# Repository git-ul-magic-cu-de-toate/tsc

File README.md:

<!-- readme-generat -->
<div align="center">

# 📚 TSC

*Arhivă de materiale din ani anteriori · Facultatea de Automatică și Calculatoare (ACS), UNSTPB*

</div>

---

## 👋 Despre acest repo

Acest repository adună **materialele pentru TSC** strânse de-a lungul mai multor ani și de la mai mulți colegi: cursuri, laboratoare, teme, subiecte de examen și parțial, rezolvări și resurse suplimentare.

Scopul lui este să fie un punct de pornire pentru cei care parcurg materia în anii următori. Materialele provin din Anul 3, Sem. 2 · Anul 4, Sem. 2.

> 💡 **Sfat:** începe cu directoarele `curs` / `cursuri` pentru teorie, apoi `laboratoare` pentru practică, iar spre final uită-te la `examen` și `partial` ca să vezi ce se cere de obicei.

## 🗂️ Ce găsești aici

| Director | Ce conține | Fișiere | Dimensiune |
|---|---|---:|---:|
| 📁 `colocviu/` | Colocviu: subiecte și rezolvări | 26 | 20.0 MB |
| 📁 `curs/` | Cursuri: slide-uri, PDF-uri și notițe | 17 | 43.8 MB |
| 📁 `diverse/` | Diverse: resurse care nu se încadrează în celelalte categorii | 2 | 53.0 MB |
| 📁 `labs/` | Laboratoare: enunțuri, resurse și rezolvări | 126 | 31.2 MB |
| 📁 `old/` | Materiale din ani anteriori | 66 | 54.6 MB |
| 📁 `proiect/` | Teme și proiecte | 29 | 14.1 MB |
| 📁 `subiecte/` | Subiecte (examen/parțial/colocviu) | 7 | 2.1 MB |
| 📁 `tsc/` |  | 0 | 0 B |

## 🌳 Structura repo-ului

```text
tsc/
├── colocviu/                                   # Colocviu: subiecte și rezolvări
│   └── … încă 26 fișiere
├── curs/                                       # Cursuri: slide-uri, PDF-uri și notițe
│   ├── Anul 3 - Sem 2/                         # 1 fișiere (pdf×1)
│   │   └── pdf/                                # Materiale în format PDF
│   ├── teste_2024/                             # 4 fișiere (pdf×4)
│   │   └── … încă 4 fișiere
│   └── … încă 12 fișiere
├── diverse/                                    # Diverse: resurse care nu se încadrează în celelalte categorii
│   └── Anul 3 - Sem 2/                         # 2 fișiere (pdf×2)
│       └── … încă 2 fișiere
├── labs/                                       # Laboratoare: enunțuri, resurse și rezolvări
│   ├── Anul 3 - Sem 2/                         # 72 fișiere (py×24, png×20, js×6)
│   │   ├── lab05/                              # Laboratorul 5
│   │   ├── lab06/                              # Laboratorul 6
│   │   ├── lab07/                              # Laboratorul 7
│   │   └── lab08/                              # Laboratorul 8
│   ├── lab07/                                  # Laboratorul 7
│   │   └── tree-traversal/                   
│   ├── pdf lab tsc/                            # 10 fișiere (pdf×10)
│   │   └── … încă 10 fișiere
│   ├── SparkFun-Eagle-Libraries-main/          # 39 fișiere (lbr×33, png×3, zip×1)
│   │   ├── SparkFun-Eagle-Libraries-main/      # 38 fișiere (lbr×33, png×3, md×1)
│   │   └── … încă 1 fișiere
│   └── … încă 3 fișiere
├── old/                                        # Materiale din ani anteriori
│   ├── Cheatsheets/                            # 1 fișiere (pdf×1)
│   │   └── … încă 1 fișiere
│   ├── Grile/                                  # 1 fișiere (pdf×1)
│   │   └── … încă 1 fișiere
│   ├── lab1/                                   # Laboratorul 1
│   │   ├── adafruit-Adafruit-Eagle-Library-4abf84c/  # 3 fișiere (md×1, lbr×1, txt×1)
│   │   └── … încă 24 fișiere
│   ├── Proiect/                                # Teme și proiecte
│   │   └── … încă 26 fișiere
│   ├── Subiecte Examen/                        # Subiecte (examen/parțial/colocviu)
│   │   └── … încă 5 fișiere
│   └── Teorie/                                 # 4 fișiere (pdf×4)
│       ├── Curs & Lab/                         # 2 fișiere (pdf×2)
│       └── Extra/                              # 2 fișiere (pdf×2)
├── proiect/                                    # Teme și proiecte
│   ├── Anul 3 - Sem 2/                         # 2 fișiere (pdf×1, txt×1)
│   │   ├── Minea_RaduStefan_334CA_before_deadline/  # 1 fișiere (txt×1)
│   │   └── … încă 1 fișiere
│   ├── hector_watch/                           # 1 fișiere (lbr×1)
│   │   └── … încă 1 fișiere
│   └── … încă 26 fișiere
├── subiecte/                                   # Subiecte (examen/parțial/colocviu)
│   ├── Anul 3 - Sem 2/                         # 6 fișiere (pdf×3, jpeg×2, jpg×1)
│   │   └── serie_necunoscuta/                  # Materiale a căror serie nu a putut fi identificată
│   └── … încă 1 fișiere
└── tsc/                                      
```

## 🧭 Cum te orientezi

- Seriile **CA, CB, CC, CD** (anii 1–3) și direcțiile **C1–C5** (anul 4) au profesori și cerințe diferite; unde seria era cunoscută, materialele sunt grupate pe serie.
- Directoarele `serie_necunoscuta` conțin materiale a căror serie nu a putut fi stabilită.
- Directoarele `labNN` / `Laborator NN` corespund laboratoarelor în ordine cronologică.
- Fișierele cu același nume dar conținut diferit au fost păstrate (de exemplu în `duplicate/` sau cu sufixul `__local`), ca să nu se piardă nimic.

## 📊 Pe scurt

- **277** fișiere, **218.9 MB** în total
- Tipuri frecvente: `.pdf` ×48 · `.lbr` ×36 · `.jpg` ×28 · `.png` ×25 · `.py` ×24 · `.job` ×14

## ⚠️ De reținut

- Materialele provin din ani și de la profesori diferiți; cerințele, baremele și tehnologiile pot fi diferite față de anul curent.
- Rezolvările și temele colegilor sunt doar pentru **studiu și inspirație**. Folosește-le cu responsabilitate și respectă regulile de integritate academică ale materiei.
- Pot exista greșeli sau materiale depășite. Verifică mereu cu cerințele oficiale ale cursului.

## 🤝 Contribuții

Ai materiale noi, corecturi sau vrei să ajuți la completarea arhivei? Scrie-mi pe email:

📧 **[sciencepc@yahoo.com](mailto:sciencepc@yahoo.com)**

Mulțumim tuturor celor care au contribuit! 💙

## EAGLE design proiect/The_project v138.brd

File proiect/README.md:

# Pasi de implementare

## 1. Acomodarea cu tematica 
- intelegere enunt si descarcare biblioteci necesare

## 2. Schematic
- am incercat sa fie cat mai asemanator cu imaginea pdf pusa pe ocw

## 3. PCB
- la generarea pcb-ului pe baza schematicului, piesele erau deja puse. 
- singurul lucru care a fost de modificat aici a fost forma butoanelor si a adaptorului. 
- am inceput cu butoanele caci au fost mai simplu. am incercat sa ma tin cat mai aproape de dimensiunile din datasheet-uri. ca sa am dimensiunile convenabile am setat gridul la 0.1 mm pentru o precizie sporita.
- acelasi lucru si la adaptorul lcd, unde am facut cateva calcule spre aflarea tuturor dimensiunilor necesare. aici a trebuit sa modific schematicul adaptorului, pinii MP1 si MP2 nefiind necesari.

## 4. Pregatire pentru "asamblare"
- am grupat componentele dupa cum erau grupate in schematic, pentru o asezare mai usoara pe planul ceasului.
- am folosit mirror pentru a pune componentele de pe bottom conform cerintei, asta inca din acest punct, pentru a vizualiza mai usor planurile

## 5. Forma ceas
- apoi am creat forma ceasului, la fel, cu multe ajustari, dupa dimensiuni (am incercat sa fac sa intre in carcasa).

## 6. GND
- am creat planul de masa cu polygon pour si linie care se poate curba, incercand cu greu sa tin conturul ceasului. copy-paste pentru bottom, selectat impruna si redenumit (legat) la GND.

## 7. Punere elemente
- am pus toate elementele in interiorul formei de ceas, incercand pe cat posibil sa pastrez restrictiile (condensatoarele fiecarui tip de piesa cat mai aproape de pini) (evebtual asa si la rezistente). 
- am pus antena pe mijloc, la margini sd-reader-ul si usb-ul, pe langa si celelalte piese, la fel, am incercat sa nu pun nor-flash sub antena pe planul de desesubt.

## 8. Finisare PCB
- am taiat forma de ceas, stergand pcb-ul, ramanand numai cercul ceasului cu planurile de masa si piesele.

## 9. Rutare
- am trecut de data aceasta la auto-route, dupa lungi incercari de a ruta manual si a reaseza piesele pentru o rutare manuala mai usoara.
- si la auto-route a trebuit sa rearanjez piesele de cateva ori (respectand restrictiile) pentru o eficienta mai sportita (88-100% routing).
chiar si asa am avut 5 air-wires.

## 10. Ajustare dupa auto-route
- am inlocuit grosimea firelor de putere (GND, VIBE-OUT, VBUS, VUSB, 3V3 etc). in acest proces mi-au aparut multe overlap-uri.
- acest lucru l-am facut ori schimbat grosmiea firului din proprieteti, ori stergandu-l si trasandu-l la loc, acolo unde am avut loc.
- pe anumite portiuni am combinatie de 0.127 - 0.3 mm

## 11. Altele
- am un overlap la un footprint care nu a fost realizat sau modificat de mine.

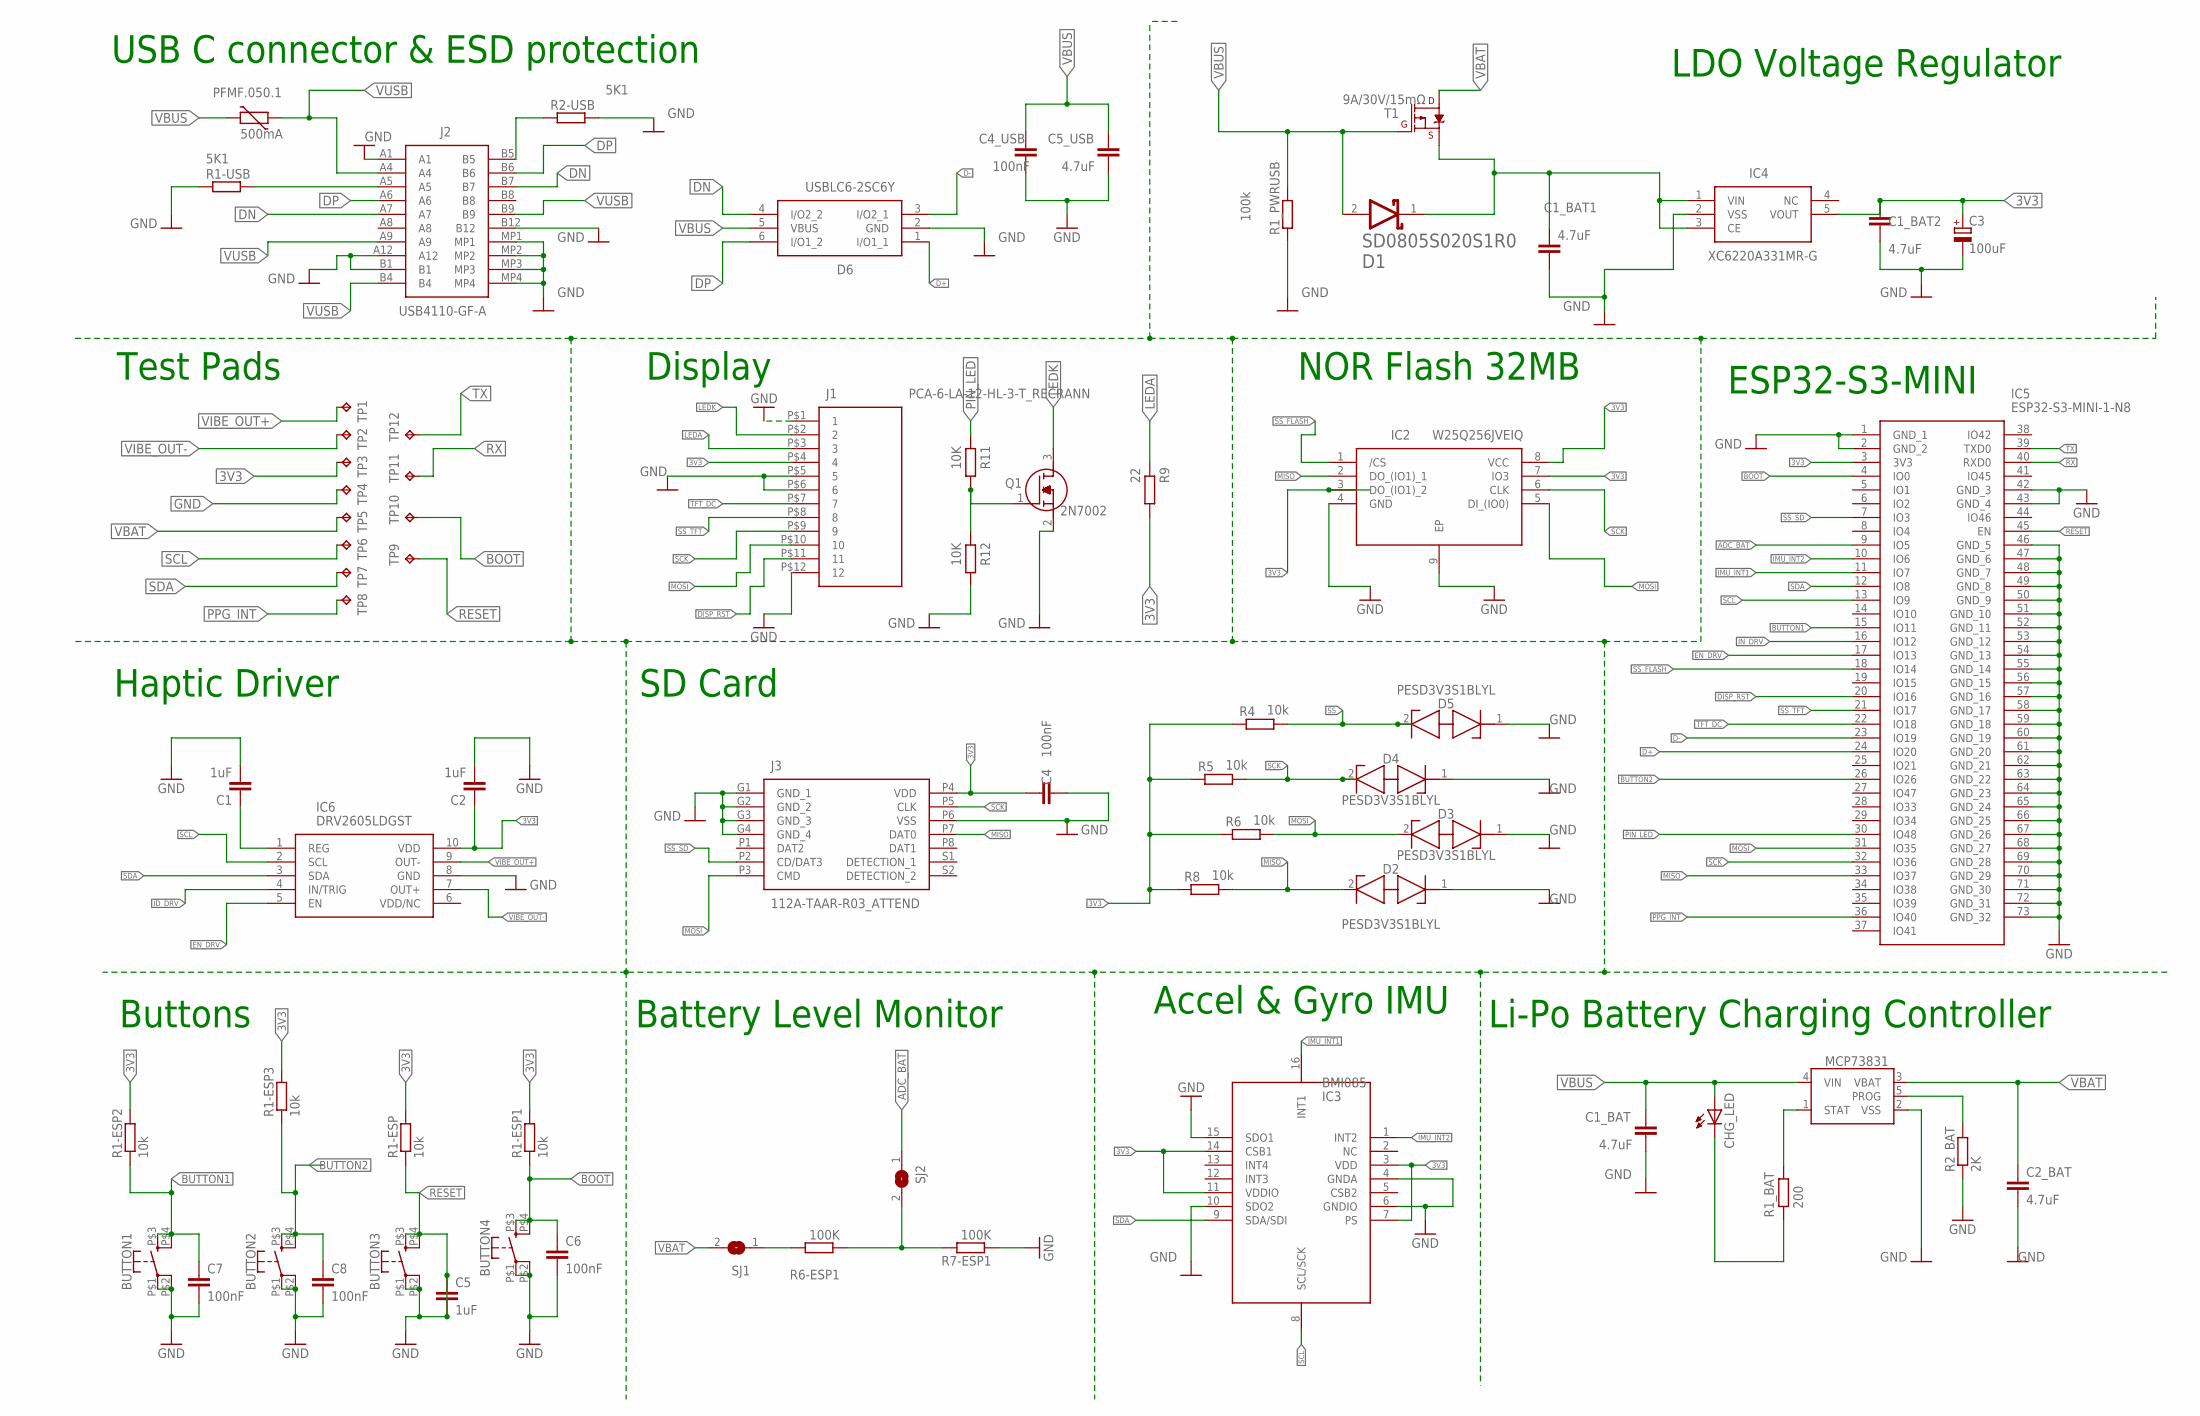
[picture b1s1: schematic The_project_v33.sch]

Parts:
BUTTON1, BUTTON2, BUTTON3, BUTTON4: SPARKFUN-SWITCHES_MOMENTARY-SWITCH-SPST-2; RRR
C1, C2, C5: 1uF; EAGLE-LTSPICE_C0402
C1_BAT, C2_BAT: 4.7uF; EAGLE-LTSPICE_C0402
C1_BAT1, C1_BAT2, C5_USB: 4.7uF; RCL_C0603
C3: 100uF; CT3528
C4, C6, C7, C8: 100nF; EAGLE-LTSPICE_C0402
C4_USB: 100nF; RCL_C0603
CHG_LED: ADAFRUIT_LEDCHIP-LED0603; ADAFRUIT_CHIP-LED0603
D1: AVX---SD0805S020S1R0_AVX_SD0805S020S1R0AVX_SD0805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; AVX---SD0805S020S1R0_AVX_SD0805S020S1R0_0
D2, D3, D4, D5: PESD3V3S1BLYL; PESD5V0S1BL315
D6: USBLC6-2SC6Y; SOT95P280X145-6N
IC2: W25Q256JVEIQ; SON127P800X600X80-9N
IC3: BMI085
IC4: XC6220A331MR-G; SOT95P280X120-5N
IC5: ESP32-S3-MINI-1-N8; ESP32S3MINI1N8
IC6: DRV2605LDGST; SOP50P490X110-10N
J1: PCA-6-LA-12-HL-3-T_RECRANN; LCD
J2: USB4110-GF-A; USB4110GFA
J3: 112A-TAAR-R03_ATTEND; 112ATAARR03ATTEND
MCP73831: SPARKFUN-IC-POWER_MCP73831; SPARKFUN-IC-POWER_SOT23-5
PFMF.050.1: 500mA; VARISTOR_CT/CN1812
Q1: 2N7002; SOT96P240X120-3N
R1-ESP, R1-ESP1, R1-ESP2, R1-ESP3, R4, R5, R6, R8: 10k; EAGLE-LTSPICE_R0402
R1-USB, R2-USB: 5K1; EAGLE-LTSPICE_R0402
R1_BAT: 200; EAGLE-LTSPICE_R0402
R1_PWRUSB: 100k; EAGLE-LTSPICE_R0402
R2_BAT: 2K; EAGLE-LTSPICE_R0402
R6-ESP1, R7-ESP1: 100K; EAGLE-LTSPICE_R0402
R9: 22; EAGLE-LTSPICE_R0402
R11, R12: 10K; EAGLE-LTSPICE_R0402
SJ1, SJ2: SJ
T1: 9A/30V/15mΩ; SPARKFUN-DISCRETESEMI_SOT23-3
TP1, TP2, TP3, TP4, TP5, TP6, TP7, TP8, TP9, TP10, TP11, TP12: TPTP20R; TP20R

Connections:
3V3: C1_BAT2.1, C2.1, C3.+, C4.1, IC2.3 (DO_(IO1)_2), IC2.7 (IO3), IC2.8 (VCC), IC3.3 (VDD), IC3.7 (PS), IC3.11 (VDDIO), IC3.14 (CSB1), IC4.5 (VOUT), IC5.3 (3V3), IC6.10 (VDD), J1.P$4 (4), J3.P4 (VDD), R1-ESP.2, R1-ESP1.2, R1-ESP2.2, R1-ESP3.2, R4.1, R5.1, R6.1, R8.1, R9.1, TP3.TP
ADC_BAT: IC5.9 (IO5), SJ2.1
BOOT: BUTTON4.P$3 (3), BUTTON4.P$4 (4), C6.1, IC5.4 (IO0), R1-ESP1.1, TP10.TP
BUTTON1: BUTTON1.P$3 (3), BUTTON1.P$4 (4), C7.1, IC5.15 (IO11), R1-ESP2.1
BUTTON2: BUTTON2.P$3 (3), BUTTON2.P$4 (4), C8.1, IC5.26 (IO26), R1-ESP3.1
D+: IC5.24 (IO20)
D-: IC5.23 (IO19)
DISP_RST: IC5.20 (IO16), J1.P$11 (11)
DN: J2.A7, J2.B7
DP: J2.A6, J2.B6
EN_DRV: IC5.17 (IO13), IC6.5 (EN)
GND: BUTTON1.P$1 (1), BUTTON1.P$2 (2), BUTTON2.P$1 (1), BUTTON2.P$2 (2), BUTTON4.P$1 (1), BUTTON4.P$2 (2), C1.2, C1_BAT.2, C1_BAT1.2, C1_BAT2.2, C2.2, C2_BAT.2, C3.-, C4.2, C4_USB.2, C5_USB.2, C6.2, C7.2, C8.2, D2.1 (K1), D3.1 (K1), D4.1 (K1), D5.1 (K1), D6.2 (GND), IC2.4 (GND), IC2.9 (EP), IC3.4 (GNDA), IC3.6 (GNDIO), IC3.10 (SDO2), IC3.15 (SDO1), IC4.2 (VSS), IC5.1 (GND_1), IC5.2 (GND_2), IC5.42 (GND_3), IC5.43 (GND_4), IC5.46 (GND_5), IC5.47 (GND_6), IC5.48 (GND_7), IC5.49 (GND_8), IC5.50 (GND_9), IC5.51 (GND_10), IC5.52 (GND_11), IC5.53 (GND_12), IC5.54 (GND_13), IC5.55 (GND_14), IC5.56 (GND_15), IC5.57 (GND_16), IC5.58 (GND_17), IC5.59 (GND_18), IC5.60 (GND_19), IC5.61 (GND_20), IC5.62 (GND_21), IC5.63 (GND_22), IC5.64 (GND_23), IC5.65 (GND_24), IC5.66 (GND_25), IC5.67 (GND_26), IC5.68 (GND_27), IC5.69 (GND_28), IC5.70 (GND_29), IC5.71 (GND_30), IC5.72 (GND_31), IC5.73 (GND_32), IC6.8 (GND), J1.P$1 (1), J1.P$5 (5), J1.P$6 (6), J1.P$12 (12), J2.A1, J2.A12, J2.B1, J2.B12, J2.MP1, J2.MP2, J2.MP3, J2.MP4, J3.G1 (GND_1), J3.G2 (GND_2), J3.G3 (GND_3), J3.G4 (GND_4), J3.P6 (VSS), MCP73831.2 (VSS), Q1.2 (S), R1_PWRUSB.1, R2-USB.2, R2_BAT.1, R7-ESP1.1, R12.1, TP4.TP
ID_DRV: IC6.4 (IN/TRIG)
IMU_INT1: IC3.16 (INT1), IC5.11 (IO7)
IMU_INT2: IC3.1 (INT2), IC5.10 (IO6)
IN_DRV: IC5.16 (IO12)
LEDA: J1.P$3 (3), R9.2
LEDK: J1.P$2 (2), Q1.3 (D)
MISO: D2.2 (K2), IC2.2 (DO_(IO1)_1), IC5.33 (IO37), J3.P7 (DAT0), R8.2
MOSI: D3.2 (K2), IC2.5 (DI_(IO0)), IC5.31 (IO35), J1.P$10 (10), J3.P3 (CMD), R6.2
unnamed: J2.A5, R1-USB.2
unnamed: C1_BAT1.1, D1.1 (CATHODE), IC4.1 (VIN), IC4.3 (CE), T1.2 (S)
unnamed: R6-ESP1.2, SJ1.1
unnamed: Q1.1 (G), R11.1, R12.2
unnamed: R6-ESP1.1, R7-ESP1.2, SJ2.2
unnamed: J2.B5, R2-USB.1
unnamed: CHG_LED.C, R1_BAT.2
unnamed: C1.1, IC6.1 (REG)
unnamed: MCP73831.1 (STAT), R1_BAT.1
unnamed: MCP73831.5 (PROG), R2_BAT.2
PIN_LED: IC5.30 (IO48), R11.2
PPG_INT: IC5.36 (IO40), TP8.TP
RESET: BUTTON3.P$1 (1), BUTTON3.P$2 (2), BUTTON3.P$3 (3), BUTTON3.P$4 (4), C5.1, C5.2, IC5.45 (EN), R1-ESP.1, TP9.TP
RX: IC5.40 (RXD0), TP11.TP
SCK: D4.2 (K2), IC2.6 (CLK), IC5.32 (IO36), J1.P$9 (9), J3.P5 (CLK), R5.2
SCL: IC3.8 (SCL/SCK), IC5.13 (IO9), IC6.2 (SCL), TP6.TP
SDA: IC3.9 (SDA/SDI), IC5.12 (IO8), IC6.3 (SDA), TP7.TP
SS: D5.2 (K2), R4.2
SS_FLASH: IC2.1 (/CS), IC5.18 (IO14)
SS_SD: IC5.7 (IO3), J3.P2 (CD/DAT3)
SS_TFT: IC5.21 (IO17), J1.P$8 (8)
TFT_DC: IC5.22 (IO18), J1.P$7 (7)
TX: IC5.39 (TXD0), TP12.TP
VBAT: C2_BAT.1, MCP73831.3 (VBAT), SJ1.2, T1.3 (D), TP5.TP
VBUS: C1_BAT.1, C4_USB.1, C5_USB.1, CHG_LED.A, D1.2 (ANODE), MCP73831.4 (VIN), PFMF.050.1.2, R1_PWRUSB.2, T1.1 (G)
VIBE_OUT+: IC6.9 (OUT-), TP1.TP
VIBE_OUT-: IC6.7 (OUT+), TP2.TP
VUSB: J2.A4, J2.A9, J2.B4, PFMF.050.1.1

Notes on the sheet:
USB C connector & ESD protection
LDO Voltage Regulator
Test Pads
Display
NOR Flash 32MB
ESP32-S3-MINI
Haptic Driver
SD Card
Buttons
Battery Level Monitor
Accel & Gyro IMU
Li-Po Battery Charging Controller

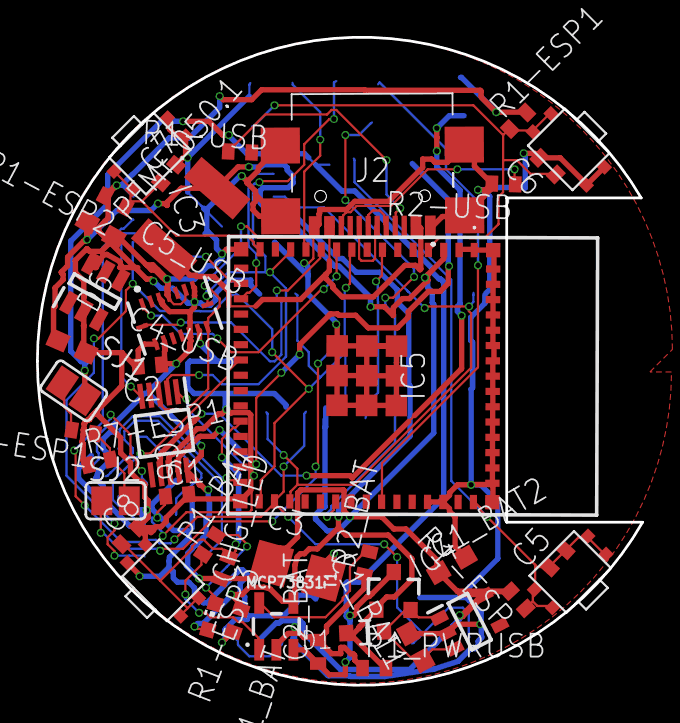
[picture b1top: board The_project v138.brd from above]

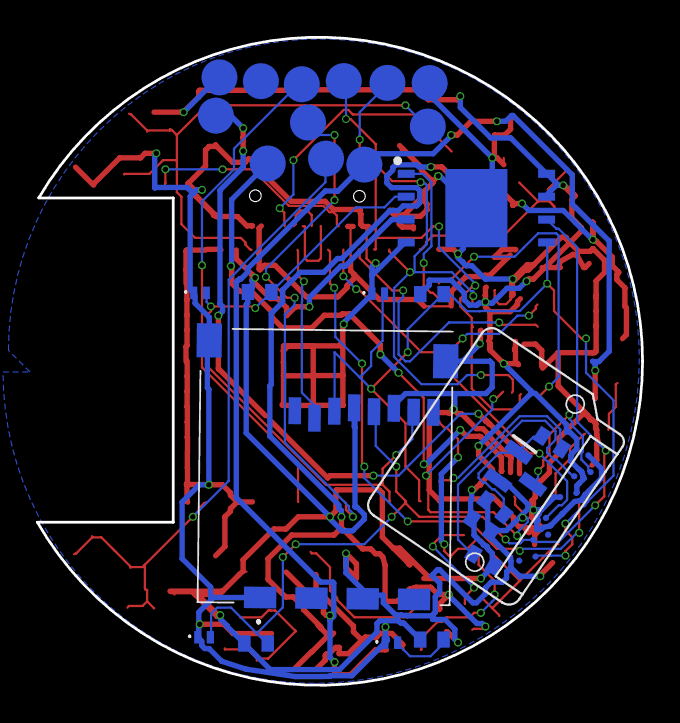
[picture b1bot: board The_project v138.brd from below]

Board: 2 copper layers, 33.6 x 36.0 mm, 69 parts (28 on the bottom side), 44 nets.
